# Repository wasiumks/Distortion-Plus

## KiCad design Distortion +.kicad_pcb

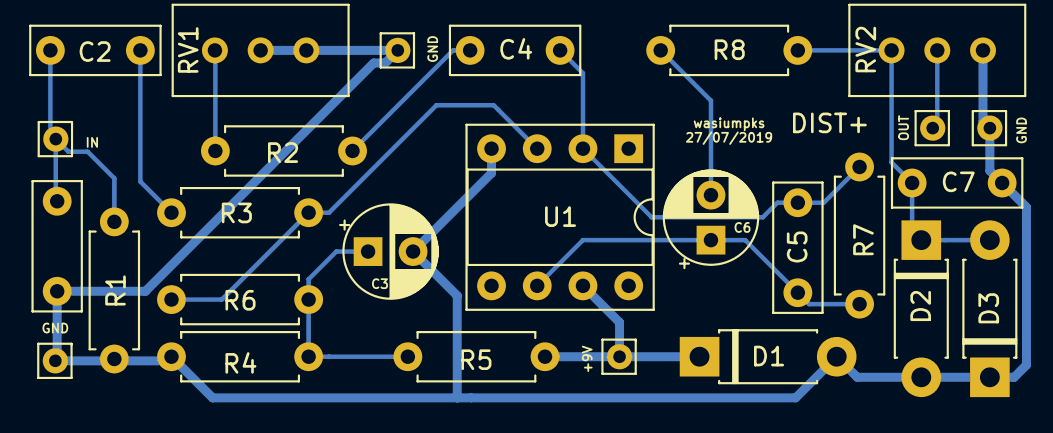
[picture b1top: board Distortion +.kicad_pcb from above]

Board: 2 copper layers, 27 parts (0 on the bottom side), 13 nets.

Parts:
+9V: Pin_D0.7mm_L6.5mm_W1.8mm_FlatFork
C1, C7: 1nF; C_Rect_L7.0mm_W2.5mm_P5.00mm
C2: 10nF; C_Rect_L7.0mm_W2.5mm_P5.00mm
C3, C6: 1uF; CP_Radial_D5.0mm_P2.50mm
C4: 47nF; C_Rect_L7.0mm_W2.5mm_P5.00mm
C5: 10pF; C_Rect_L7.0mm_W2.5mm_P5.00mm
D1: 1N4007; D_DO-41_SOD81_P7.62mm_Horizontal
D2, D3: Ge; D_DO-41_SOD81_P7.62mm_Horizontal
GND: Pin_D0.7mm_L6.5mm_W1.8mm_FlatFork
GND#2, GND#3: Pin_D0.7mm_L6.5mm_W1.8mm_FlatFork
IN: Pin_D0.7mm_L6.5mm_W1.8mm_FlatFork
OUT: Pin_D0.7mm_L6.5mm_W1.8mm_FlatFork
R1, R4, R5, R6, R7: 1M; R_Axial_DIN0207_L6.3mm_D2.5mm_P7.62mm_Horizontal
R2: 4k7; R_Axial_DIN0207_L6.3mm_D2.5mm_P7.62mm_Horizontal
R3, R8: 10k; R_Axial_DIN0207_L6.3mm_D2.5mm_P7.62mm_Horizontal
RV1: C500k; Potentiometer_Bourns_3386C_Horizontal
RV2: A50k; Potentiometer_Bourns_3386C_Horizontal
U1: LM741; DIP-8_W7.62mm_Socket

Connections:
GND: C1.2, C3.2, C7.2, D1.2, D2.2, D3.1, GND.1, GND#2.1, GND#3.1, R1.2, R4.2, RV1.1, RV1.2, RV2.3, U1.4
unnamed: +9V.1, D1.1, R5.1, U1.7
unnamed: C1.1, C2.2, IN.1, R1.1
unnamed: C2.1, R3.2
unnamed: C3.1, R4.1, R5.2, R6.1
unnamed: C4.1, C5.2, R7.2, U1.2
unnamed: C4.2, R2.1
unnamed: C5.1, C6.1, R7.1, U1.6
unnamed: C6.2, R8.2
unnamed: C7.1, D2.1, D3.2, R8.1, RV2.1
unnamed: OUT.1, RV2.2
unnamed: R2.2, RV1.3
unnamed: R3.1, R6.2, U1.3

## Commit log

2019-12-27 add files
